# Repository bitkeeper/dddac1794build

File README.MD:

This project is about creating a DAC system based on [DDDAC 1794 NOS](http://www.dddac.com/dddac1794.html) kits.
It uses a Raspberry Pi as audio source and includes a nice enclosure.

System exists out of:
* DDDAC 1794 system
 * DDDAC 1794 mainboard
 * 2 Deck DAC with Tent regulators
  * DDDAC 12V PS
  * 2 Cinemags 600/600L for audio output
* I2S audio source
 * Raspberry 3B
 * ~~Hifiberry Digi+ Pro~~
 * ~~Allo Isolator~~
 * Ian Canada Fifopi Q3 with two upgraded clocks
 * The Pi runs Moode Audio 7.0.0
 * Wired network
* Digital Inputs
  * 2 SPDIF
  * 1 Toslink
* Digital Output
  * 1 SPDIF with transformer
* Low noise 5 Volt for pi
* Separate low noise 5 Volt for isolator and the hifiberry
* Power controller for soft power down (kill power after Pi is down)
* Hifi2000 Galaxy enclosure with custom back and front panel
* OLED display with track information or source selection

More about the software install can be found in [README.MD](raspberrypi/software/README.MD).

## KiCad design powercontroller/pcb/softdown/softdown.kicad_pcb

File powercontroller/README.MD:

* attiny85 - software sketch for the attiny85
* design - initial design of the soft power off module
* pcb - scheme and pcb design for actual use

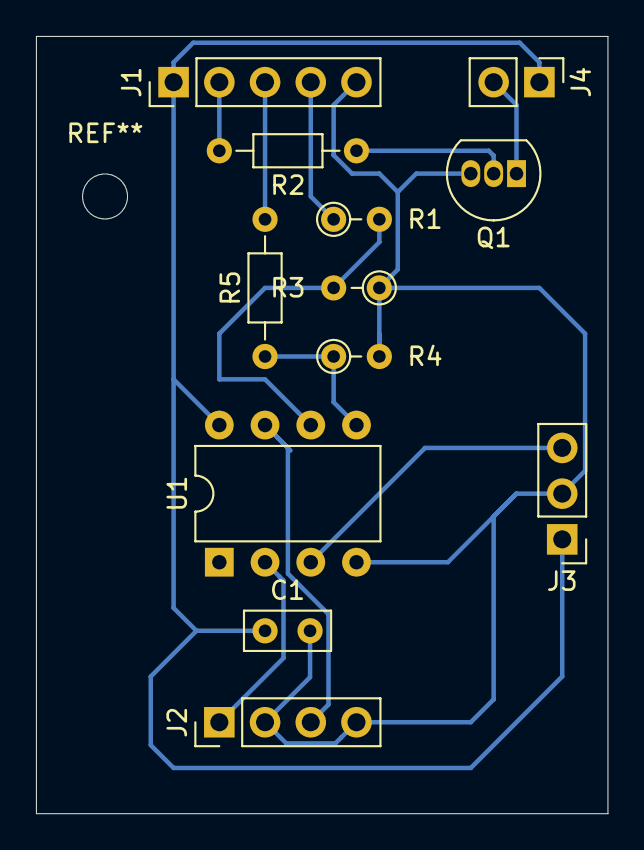
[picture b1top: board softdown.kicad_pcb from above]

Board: 2 copper layers, 31.8 x 43.2 mm, 12 parts (0 on the bottom side), 12 nets.

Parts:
C1: C; C_Rect_L4.6mm_W2.0mm_P2.50mm_MKS02_FKP02
J1: RaspberryIO; PinHeader_1x05_P2.54mm_Vertical
J2: SwitchPowerAndLed; PinHeader_1x04_P2.54mm_Vertical
J3: RelayBoard; PinHeader_1x03_P2.54mm_Vertical
J4: SwitchSourceLed; PinHeader_1x02_P2.54mm_Vertical
Q1: BC547; TO-92_Inline
R1, R3, R4: 1k; R_Axial_DIN0204_L3.6mm_D1.6mm_P2.54mm_Vertical
R2: 2k7; R_Axial_DIN0204_L3.6mm_D1.6mm_P7.62mm_Horizontal
R5: 1k; R_Axial_DIN0204_L3.6mm_D1.6mm_P7.62mm_Horizontal
U1: ATtiny85-20PU; DIP-8_W7.62mm

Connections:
+5V: C1.1, J1.1, J3.1, J4.1, U1.8
GND: C1.2, J1.5, J2.2, J2.4, J3.2, Q1.3, R3.1, R4.2, U1.4
unnamed: J4.2, Q1.1
unnamed: Q1.2, R2.1
unnamed: R1.2, R3.2, U1.6
unnamed: R4.1, R5.1, U1.5
button_pin: J2.3, U1.7
led_pin: J2.1, U1.2
pi_state: J1.3, R5.2
pwr_down_req: J1.4, R1.1
relais_pin: J3.3, U1.3
source_led: J1.2, R2.2

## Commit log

2020-04-29 added helpers for stopping and starting moode servers
2020-04-30 moode mpd tweaks ui support for moode 6.5.1
2020-04-30 added selective resample support for mpd 0.21.23
2020-04-30 add mpd-0.21.23sr to the moode mpd version selection list
2020-04-30 reduce the albumthumbnail size (simular to what moode 6.4.2 was)
2020-05-01 Added css media for better auto responsive to different dprs/dpis.
2020-05-02 add description of software mods and tweaks
2020-05-02 moved systemd files to subproject dirs
2020-05-02 Added install documentation for mOode 6.5.1
2020-05-03 Use album search priority priority OriginalRelease, OriginalYear, Date insteadof only Date
2020-05-09 Changed the way to hook in the custom css file.
2020-05-13 soundquality album overlay
2020-05-13 added documentation for the album sound quality overlay
2020-05-13 Added link to the software install documentation
2020-05-19 native lazy loading support
2020-06-28 updated selective resample pathc for mpd-0.21.24
2020-06-28 Added that there are also patches for mpd 0.21.24 and 0.21.20
2020-07-12 Restrict luma.oled tp 3.4, newer isn't compatible with py2
2020-07-12 bump mpd version to 0.21.24
2020-07-12 install mpd 0.21.24sr with moode 6.6.x
2020-07-12 updated documentation for moOde 6.6.0
2020-07-12 Add howto prevent scanning of cue files
2020-07-12 added patch mpd_tweaks for mood 6.6.x
2020-07-12 bump mpd version to 0.21.25
2020-07-12 bumpd version number of moOde to 6.6.0 and moved tweaks that are now part of the sourcetree
2020-07-15 fixed stuck on Digital 1
2020-07-21 Added support for several modes of selective resampling.
2020-07-23 example config of custom soxr recipe
2020-07-23 support for custom soxr recipes
2020-07-23 added debug message with used settings
2020-07-24 wrong attenuation calculation
2020-07-24 removed unneeded include
2020-07-24 selective resample support for the 0.22~git branch
2020-07-24 custom sox recipe support for mdp-0.22~git branch
2020-07-26 fixed patch wrong patch location
2020-07-26 fixed missing math.h
2020-07-26 updated indexes
2020-07-28 added header and correct some offsets
2020-07-28 change setting from mode to bitmask, support till 768k
2020-07-30 Updated license header.
2020-07-31 fixed target 44.1k to 48k lut use
2020-08-03 added RESET_ON_CLEAR flag
2020-08-09 updated header doc about phase_response and increased range of stopband_begin to 199%
2020-09-04 Synced with current MPD PR status
2020-09-17 patch for 384kHz support for rpi-dac|pcm1794
2020-09-17 chmod +x
2020-09-17 added kernel modules 384k patch for 5.4.51-v7+ and 5.4.51-v7l+
2020-09-17 added procedure for installing prebuild modules
2020-09-20 add patched 384k module for the 64bit kernel 5.4.61-v8+
2020-09-26 replaced wrong module snd-soc-pcm179x-codec
2020-11-13 Replaced Hifiberry Digi+ Pro and Allo Isolator by an FifoPi
2020-12-19 update to current used hardware configuration
2020-12-19 Updated to moode 7.0.0
2020-12-19 fixed typo selective resample for 705.6k
2021-10-19 Updated mpd selective resample patch for mpd 0.23.xx
2021-10-19 Fixed copy in samplerate in the 0.23 patch
    Was based on older 0.22 patch, while newer one of 0.22 already did contain that patch.
2021-10-19 [mpd] update patch to reflext that mpd rename FormatWarning to FmtWarning
